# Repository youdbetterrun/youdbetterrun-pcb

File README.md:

# You'd Better Run!

Lets you know if you can walk leisurely to catch the bus, or if you'd better run.

This repository holds the printed circuit board design files. A render of the PCB is below.

There are separate repositories for the firmware and 3D models.
- [Firmware](https://github.com/youdbetterrun/youdbetterrun-firmware): The code that runs on the microcontroller.
- [3D](https://github.com/youdbetterrun/youdbetterrun-3d): 3D models that need to be 3D printed and assembly instructions.

[Blog post about this project.](https://blog.marcelrobitaille.me/youdbetterrun/)

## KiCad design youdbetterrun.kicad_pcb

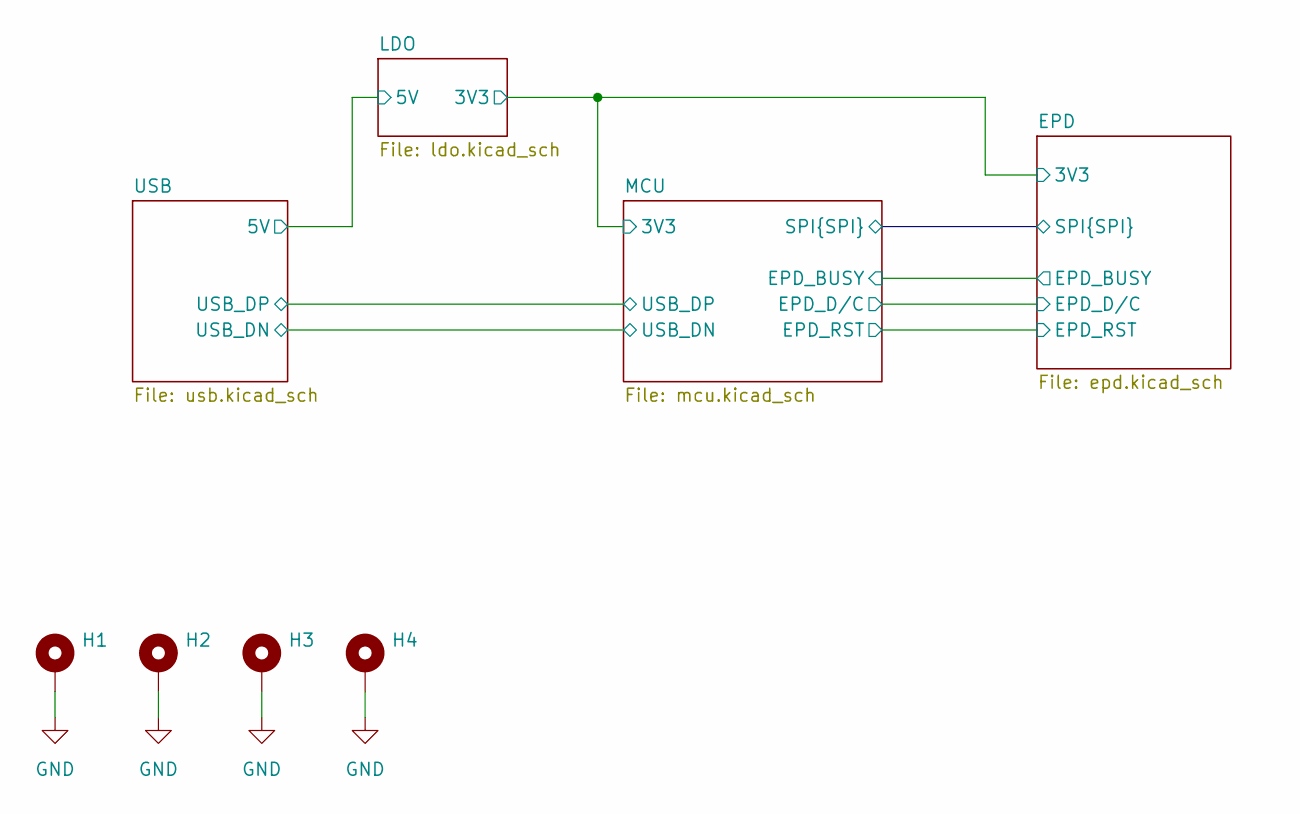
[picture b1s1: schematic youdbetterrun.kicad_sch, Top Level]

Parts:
H1, H2, H3, H4: MountingHole_Pad; MountingHole_2.2mm_M2_Pad

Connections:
GND: H1.1, H2.1, H3.1, H4.1; also elsewhere on the board

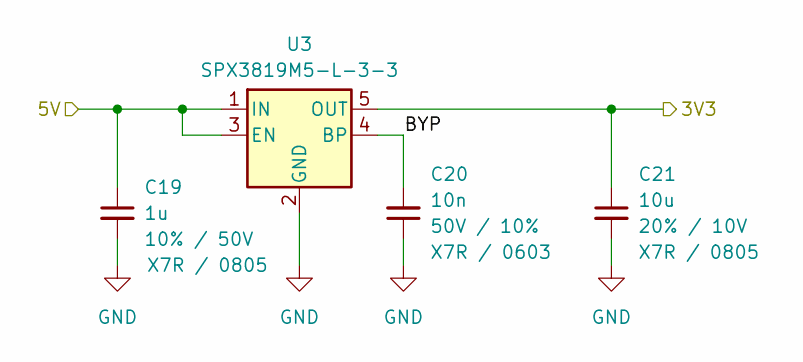
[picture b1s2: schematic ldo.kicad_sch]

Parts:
C19: 1u; C_0805_2012Metric; Tolerance 10%; Rated Voltage 50V; MPN CC0805KKX7R9BB105; LCSC Part Number C91185
C20: 10n; C_0603_1608Metric; Rated Voltage 50V; Tolerance 10%; MPN CC0603KRX7R9BB103; LCSC Part Number C100042
C21: 10u; C_0805_2012Metric; Rated Voltage 10V; Tolerance 20%; MPN CS2012X7R106M100NRE; LCSC Part Number C5189822
U3: SPX3819M5-L-3-3; SOT-23-5; MPN SPX3819M5-L-3-3/TR; LCSC Part Number C9055

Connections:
/EPD/3V3: C21.1, U3.5 (OUT); also elsewhere on the board
/LDO/BYP: C20.2, U3.4 (BP)
/USB/5V: C19.1, U3.1 (IN), U3.3 (EN); also elsewhere on the board
GND: C19.2, C20.1, C21.2, U3.2 (GND); also elsewhere on the board

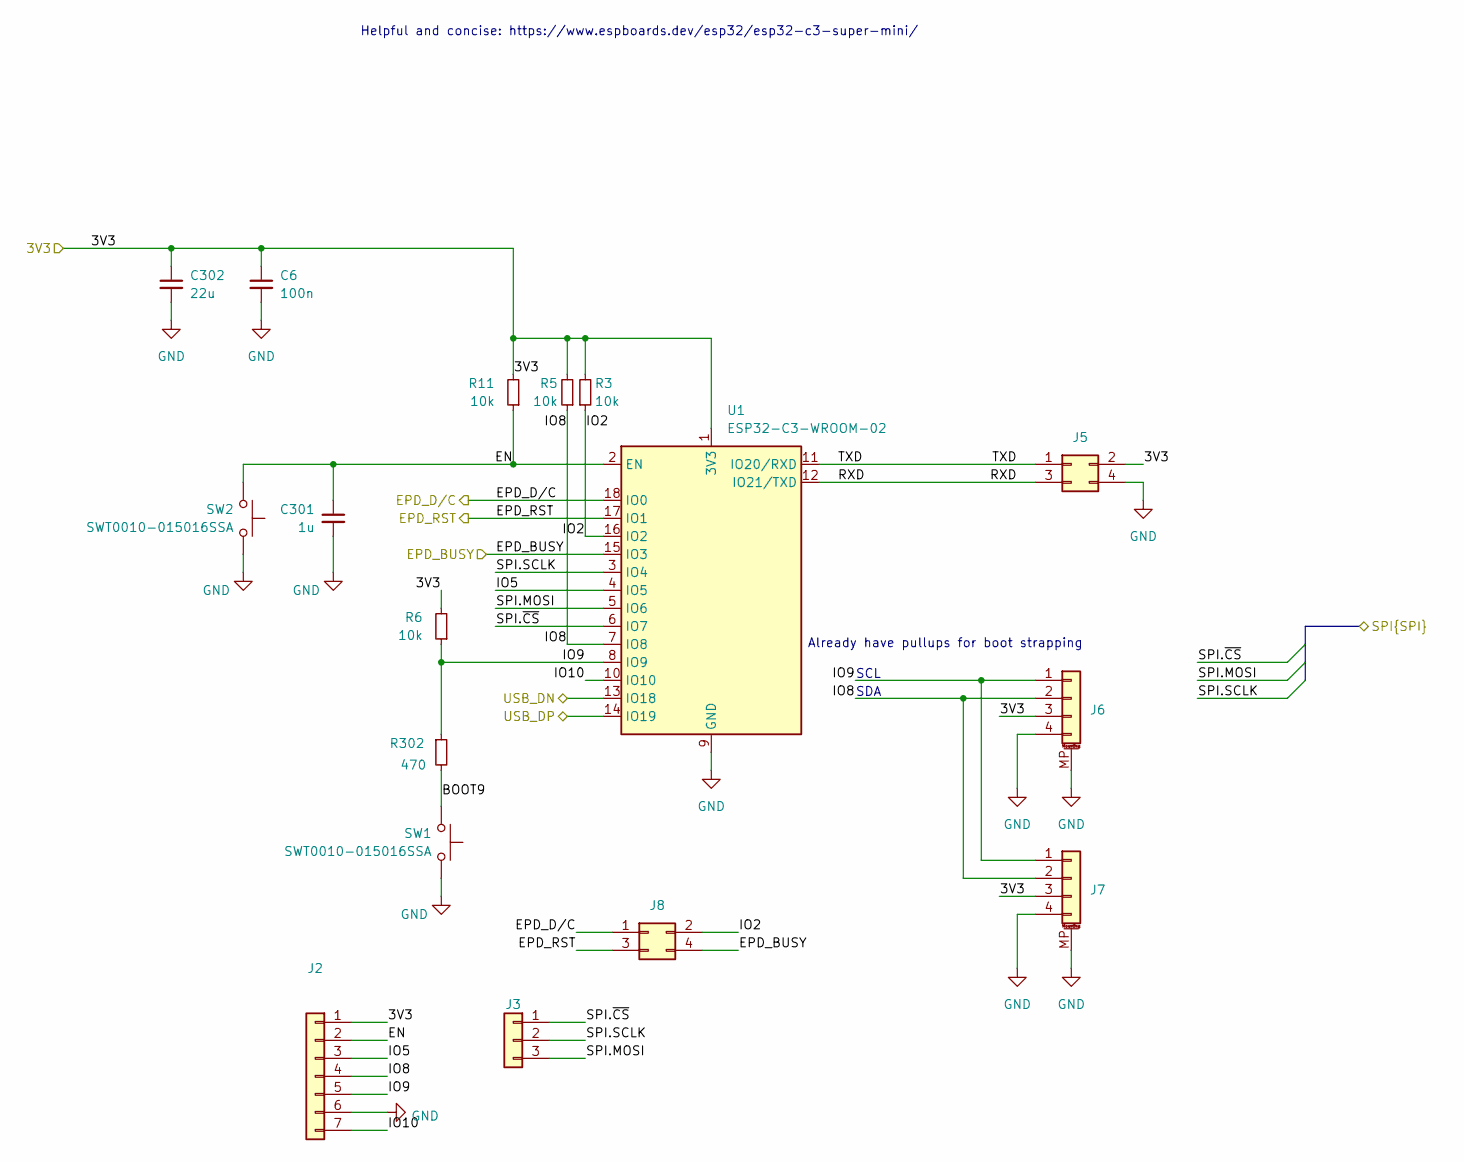
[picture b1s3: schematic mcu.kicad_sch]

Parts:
C6: 100n; C_0805_2012Metric; Rated Voltage 50V; Tolerance 10%; MPN 0805B104K500NT; LCSC Part Number C38141
C301: 1u; C_0805_2012Metric; Tolerance 10%; Rated Voltage 50V; MPN CC0805KKX7R9BB105; LCSC Part Number C91185
C302: 22u; C_0805_2012Metric
J2: Conn_01x05_Pin; PinHeader_1x07_P2.54mm_Vertical
J3: Conn_01x10_Pin; PinHeader_1x03_P2.54mm_Vertical
J5, J8: Conn_01x04; PinHeader_2x02_P2.54mm_Vertical
J6, J7: SM04B-SRSS-TB; JST_SH_SM04B-SRSS-TB_1x04-1MP_P1.00mm_Horizontal; MPN SM04B-SRSS-TB; Digikey Part Number 455-SM04B-SRSS-TBCT-ND
R3, R5, R6, R11: 10k; R_0805_2012Metric; Tolerance 1%; MPN 0805W8F1002T5E; LCSC Part Number C17414
R302: 470; R_0805_2012Metric
SW1, SW2: SWT0010-015016SSA; MPN SWT0010-015016SSA; Mouser Part Number 640-SWT0010015016SSA
U1: ESP32-C3-WROOM-02; ESP32-C3-WROOM-02_big_vias

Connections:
/EPD/3V3: C6.1, C302.1, J2.1, J5.2, J6.3, J7.3, R3.2, R5.2, R6.2, R11.2, U1.1 (3V3); also elsewhere on the board
/EPD/EPD_BUSY: J8.4, U1.15 (IO3); also elsewhere on the board
/EPD/EPD_D/C: J8.1, U1.18 (IO0); also elsewhere on the board
/EPD/EPD_RST: J8.3, U1.17 (IO1); also elsewhere on the board
/EPD/SPI.MOSI: J3.3, U1.5 (IO6); also elsewhere on the board
/EPD/SPI.SCLK: J3.2, U1.3 (IO4); also elsewhere on the board
/EPD/SPI.~CS: J3.1, U1.6 (IO7); also elsewhere on the board
/MCU/BOOT9: R302.2, SW1.2
/MCU/EN: C301.1, J2.2, R11.1, SW2.2, U1.2 (EN)
/MCU/IO2: J8.2, R3.1, U1.16 (IO2)
/MCU/IO5: J2.3, U1.4 (IO5)
/MCU/IO8: J2.4, J6.2, J7.2, R5.1, U1.7 (IO8)
/MCU/IO9: J2.5, J6.1, J7.1, R6.1, R302.1, U1.8 (IO9)
/MCU/IO10: J2.7, U1.10 (IO10)
/MCU/RXD: J5.3, U1.12 (IO21/TXD)
/MCU/TXD: J5.1, U1.11 (IO20/RXD)
/USB/USB_DN: U1.13 (IO18); also elsewhere on the board
/USB/USB_DP: U1.14 (IO19); also elsewhere on the board
GND: C6.2, C301.2, C302.2, J2.6, J5.4, J6.4, J6.MP (MountPin), J7.4, J7.MP (MountPin), SW1.1, SW2.1, U1.9 (GND), U1.19 (GND); also elsewhere on the board

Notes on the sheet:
SCL
Already have pullups for boot strapping
SDA
Helpful and concise: https://www.espboards.dev/esp32/esp32-c3-super-mini/

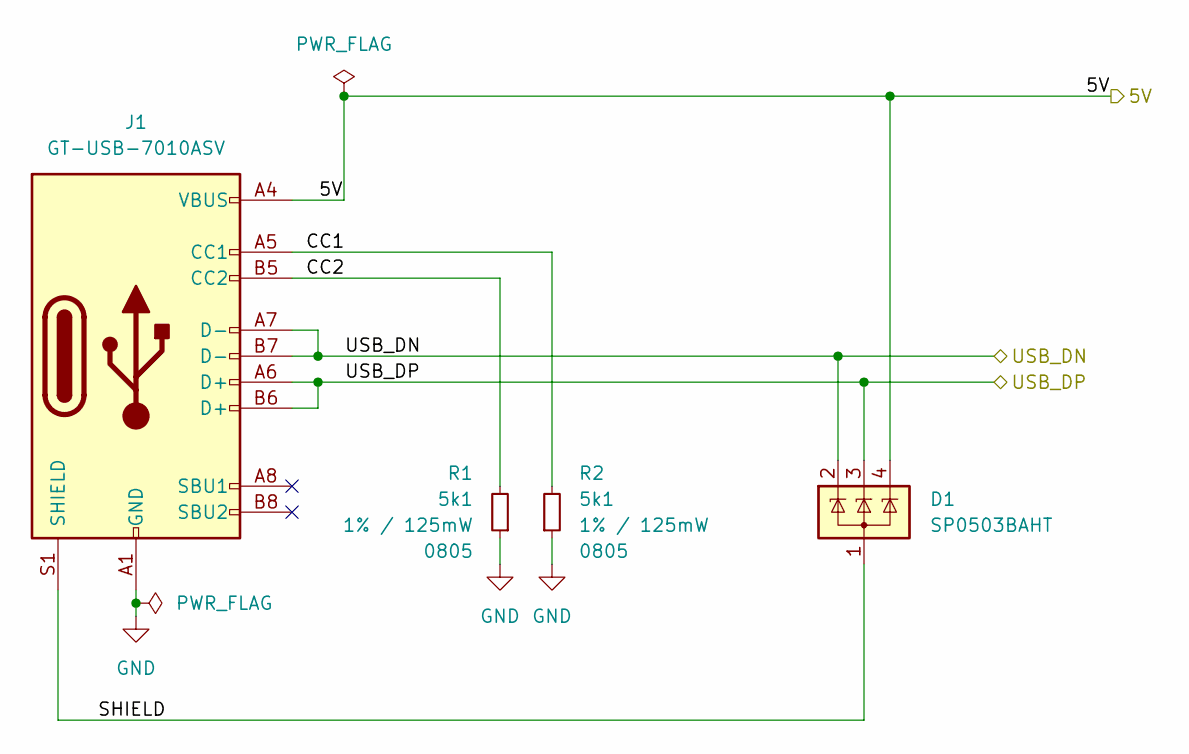
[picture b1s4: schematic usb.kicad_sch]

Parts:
D1: SP0503BAHT; SOT-143; MPN SP0503BAHTG; LCSC Part Number C7074
J1: GT-USB-7010ASV; USB_C_Receptacle_G-Switch_GT-USB-7010ASV; MPN G-Switch; LCSC Part Number C2988369
R1, R2: 5k1; R_0805_2012Metric; Tolerance 1%; MPN 0805W8F5101T5E; LCSC Part Number C27834

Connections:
/USB/5V: D1.4 (K), J1.A4 (VBUS), J1.A9 (VBUS), J1.B4 (VBUS), J1.B9 (VBUS); also elsewhere on the board
/USB/CC1: J1.A5 (CC1), R2.2
/USB/CC2: J1.B5 (CC2), R1.2
/USB/SHIELD: D1.1 (A), J1.S1 (SHIELD)
/USB/USB_DN: D1.2 (K), J1.A7 (D-), J1.B7 (D-); also elsewhere on the board
/USB/USB_DP: D1.3 (K), J1.A6 (D+), J1.B6 (D+); also elsewhere on the board
GND: J1.A1 (GND), J1.A12 (GND), J1.B1 (GND), J1.B12 (GND), R1.1, R2.1; also elsewhere on the board

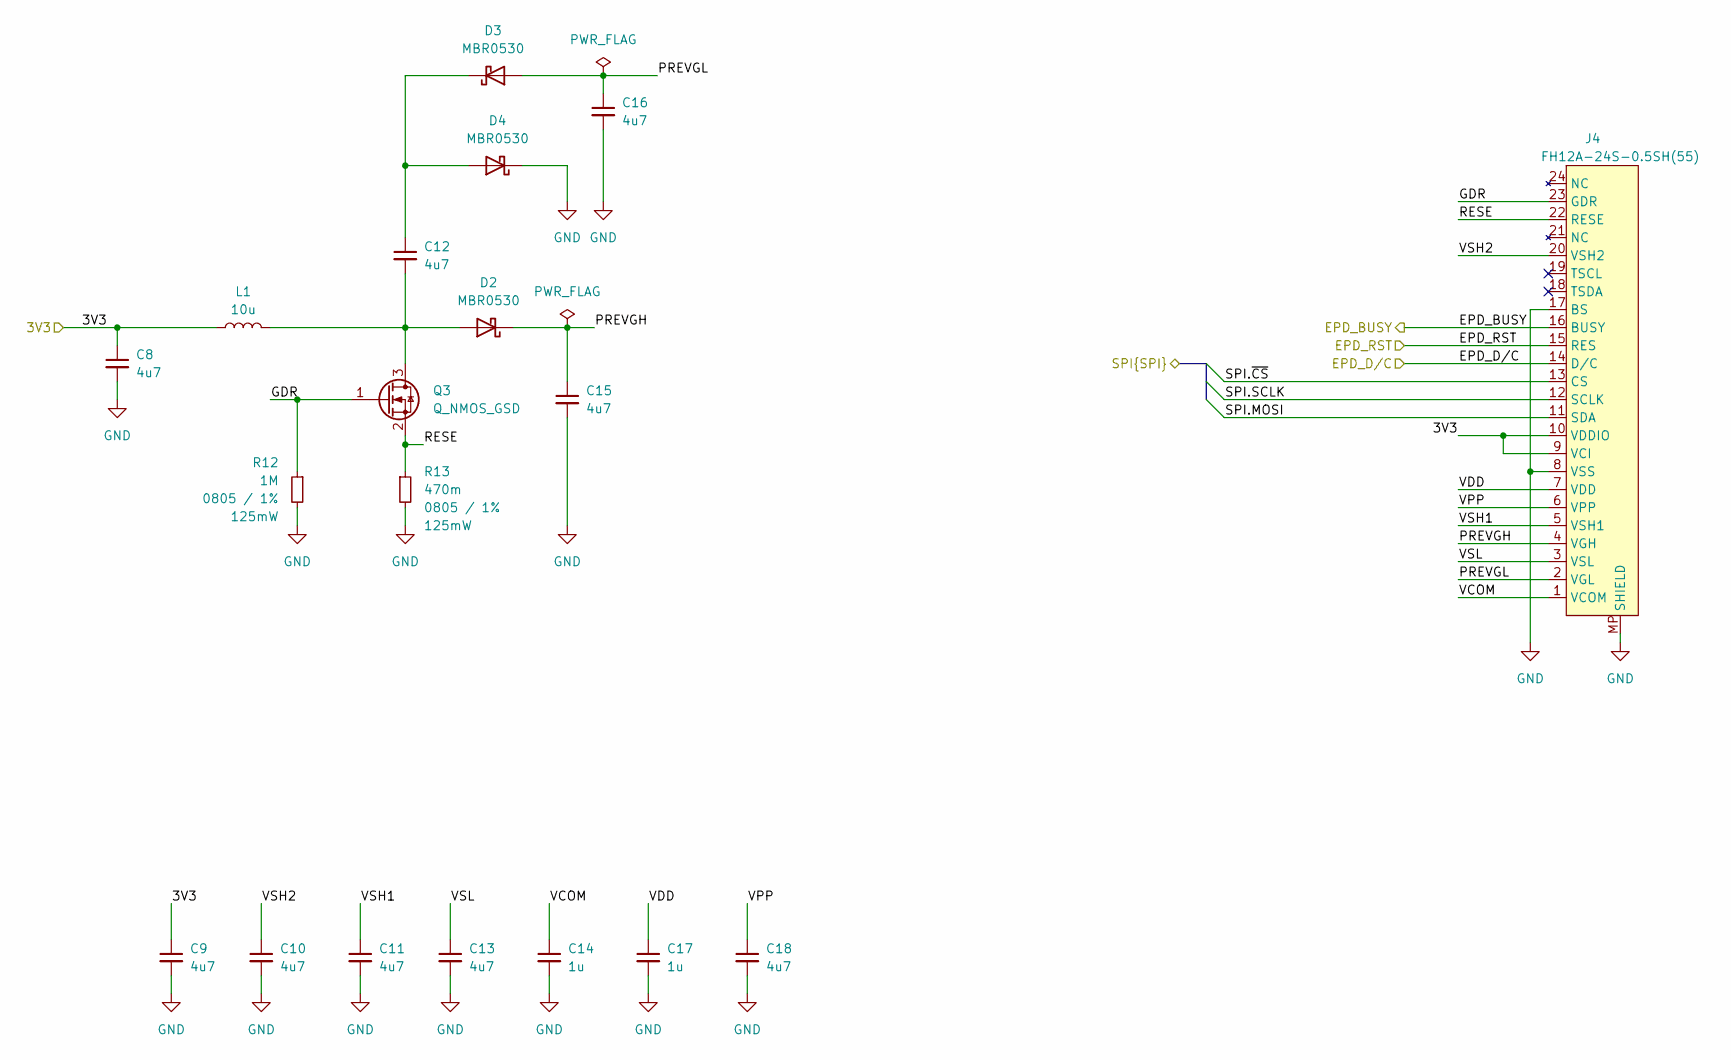
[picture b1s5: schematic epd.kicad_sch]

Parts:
C8, C9, C10, C11, C12, C13, C15, C16, C18: 4u7; C_0805_2012Metric; Tolerance 10%; Rated Voltage 50V; MPN CL21A475KBQNNNE; LCSC Part Number C98192
C14, C17: 1u; C_0805_2012Metric; Tolerance 10%; Rated Voltage 50V; MPN CC0805KKX7R9BB105; LCSC Part Number C91185
D2, D3, D4: MBR0530; D_SOD-123; MPN MBR0530; LCSC Part Number C77336
J4: FH12A-24S-0.5SH(55); Hirose_FH12-24S-0.5SH_1x24-1MP_P0.50mm_Horizontal; MPN FH12A-24S-0.5SH(55); LCSC Part Number C506794
L1: 10u; L_4x4x2.6; MPN YJYCOIN YNR4026-100M; LCSC Part Number C497803
Q3: Q_NMOS_GSD; SOT-323_SC-70; MPN SI1308EDL-T1-GE3; LCSC Part Number C469327
R12: 1M; R_0805_2012Metric; Tolerance 1%; MPN 0805W8F1004T5E; LCSC Part Number C17514
R13: 470m; R_0805_2012Metric; Tolerance 1%; MPN 0805W8F470LT5E; LCSC Part Number C25040

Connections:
/EPD/3V3: C8.1, C9.1, J4.9 (VCI), J4.10 (VDDIO), L1.1; also elsewhere on the board
/EPD/EPD_BUSY: J4.16 (BUSY); also elsewhere on the board
/EPD/EPD_D/C: J4.14 (D/C); also elsewhere on the board
/EPD/EPD_RST: J4.15 (RES); also elsewhere on the board
/EPD/GDR: J4.23 (GDR), Q3.1 (G), R12.1
/EPD/PREVGH: C15.1, D2.1 (K), J4.4 (VGH)
/EPD/PREVGL: C16.1, D3.2 (A), J4.2 (VGL)
/EPD/RESE: J4.22 (RESE), Q3.2 (S), R13.1
/EPD/SPI.MOSI: J4.11 (SDA); also elsewhere on the board
/EPD/SPI.SCLK: J4.12 (SCLK); also elsewhere on the board
/EPD/SPI.~CS: J4.13 (CS); also elsewhere on the board
/EPD/VCOM: C14.1, J4.1 (VCOM)
/EPD/VDD: C17.1, J4.7 (VDD)
/EPD/VPP: C18.1, J4.6 (VPP)
/EPD/VSH1: C11.1, J4.5 (VSH1)
/EPD/VSH2: C10.1, J4.20 (VSH2)
/EPD/VSL: C13.1, J4.3 (VSL)
GND: C8.2, C9.2, C10.2, C11.2, C13.2, C14.2, C15.2, C16.2, C17.2, C18.2, D4.1 (K), J4.8 (VSS), J4.17 (BS), J4.MP (SHIELD), R12.2, R13.2; also elsewhere on the board
unnamed: C12.2, D2.2 (A), L1.2, Q3.3 (D)
unnamed: C12.1, D3.1 (K), D4.2 (A)

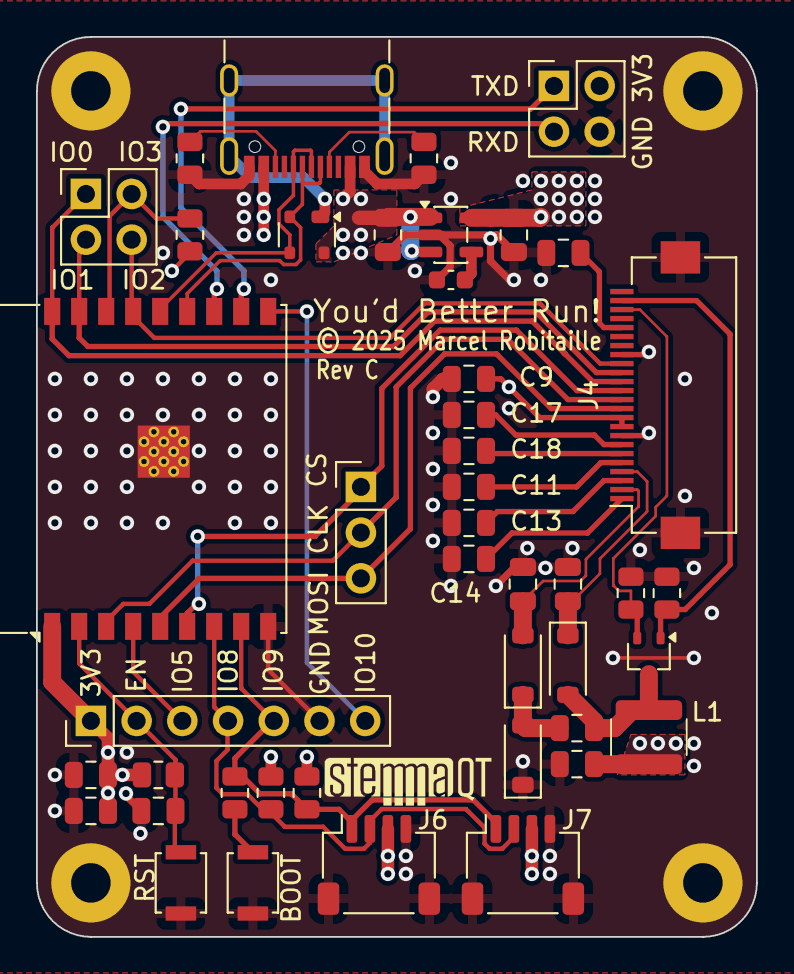
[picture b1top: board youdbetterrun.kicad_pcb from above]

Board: 4 copper layers, 40.0 x 50.0 mm, 49 parts (0 on the bottom side), 36 nets.

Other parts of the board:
StemmaQTLogo: STEMMAQT

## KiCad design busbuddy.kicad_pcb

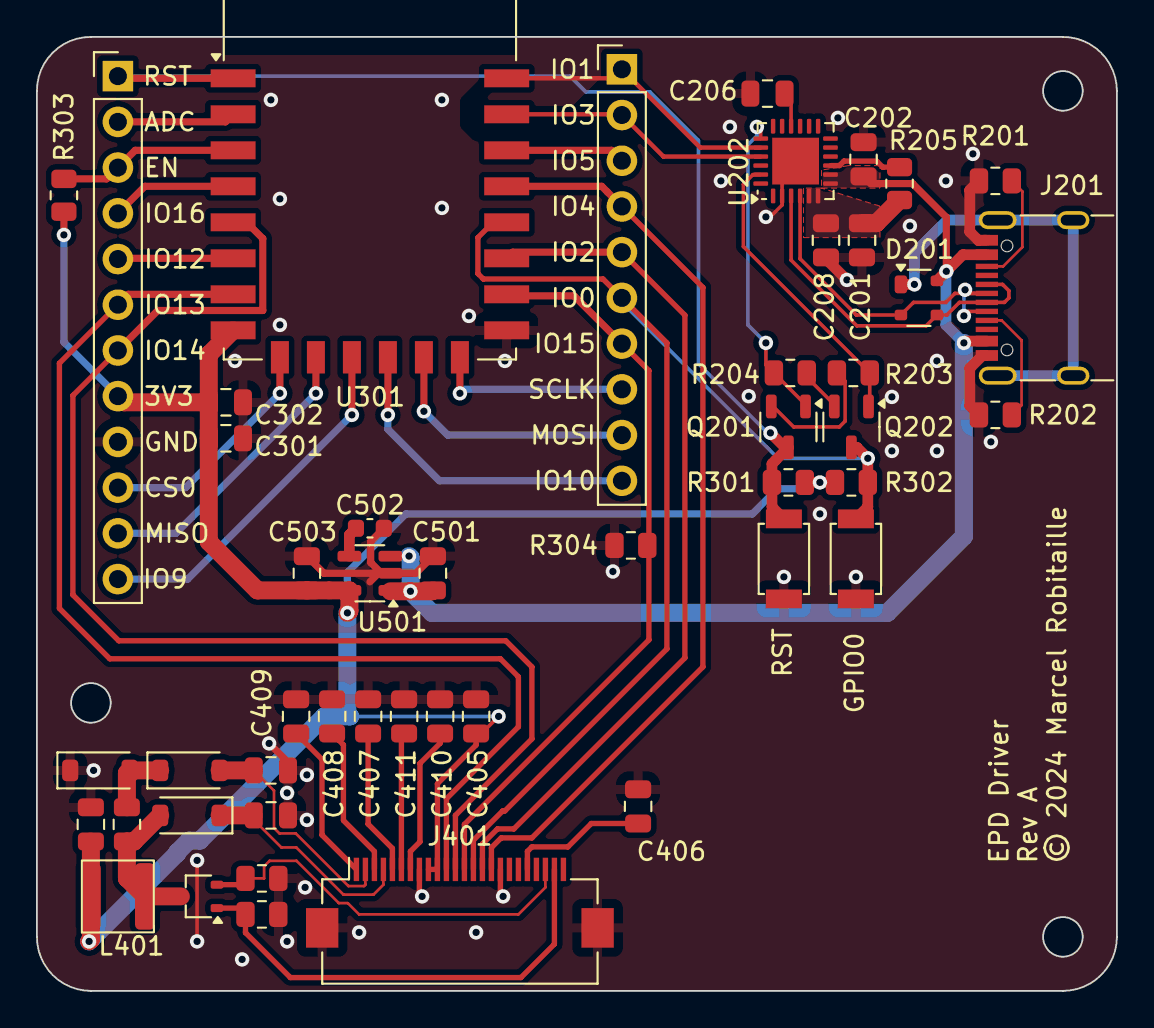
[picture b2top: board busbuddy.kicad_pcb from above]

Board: 4 copper layers, 60.0 x 53.0 mm, 48 parts (0 on the bottom side), 48 nets.

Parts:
C201, C206, C401, C402, C403, C404, C405, C406, C407, C408, C411: 4u7; C_0805_2012Metric
C202, C208, C302: 100n; C_0805_2012Metric
C301, C503: 10u; C_0805_2012Metric
C409, C410, C501: 1u; C_0805_2012Metric
C502: 10n; C_0603_1608Metric
D201: SP0503BAHT; SOT-143
D401, D402, D403: MBR0530; D_SOD-123
J201: GT-USB-7010ASV; USB_C_Receptacle_G-Switch_GT-USB-7010ASV
J301: Conn_01x05_Pin; PinHeader_1x12_P2.54mm_Vertical
J302: Conn_01x10_Pin; PinHeader_1x10_P2.54mm_Vertical
J401: FH12A-24S-0.5SH(55); Hirose_FH12-24S-0.5SH_1x24-1MP_P0.50mm_Horizontal
L401: 10u; L_4x4x2.6
Q201, Q202: S8050; SOT-23-3
Q401: Q_NMOS_GSD; SOT-323_SC-70
R201, R202: 5k1; R_0805_2012Metric
R203, R204: 12k; R_0805_2012Metric
R205: 4k7; R_0805_2012Metric
R301, R302, R303, R304: 10k; R_0805_2012Metric
R401: 470m; R_0805_2012Metric
R402: 1M; R_0805_2012Metric
SW301, SW302: TS-1088R-02026; TS-1088R-02026_SW_SMD_3x4mm
U202: CP2104; QFN-24-1EP_4x4mm_P0.5mm_EP2.6x2.6mm
U301: ESP-12F; ESP-12E
U501: SPX3819M5-L-3-3; SOT-23-5

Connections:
/EPD/3V3: C301.1, C302.1, C402.1, C405.1, C503.1, J301.8, J401.9 (VCI), J401.10 (VDDIO), L401.1, R301.2, R302.1, R303.2, U301.8 (VCC), U501.5 (OUT)
/EPD/EPD_BUSY: J302.4, J401.16 (BUSY), U301.19 (GPIO4)
/EPD/EPD_D/C: J302.6, J401.14 (D/C), Q202.3 (C), R302.2, SW302.2, U301.18 (GPIO0)
/EPD/EPD_RST: J302.5, J401.15 (RES), U301.17 (GPIO2)
/EPD/GDR: J401.23 (GDR), Q401.1 (G), R402.1
/EPD/PREVGH: C401.1, D401.1 (K), J401.4 (VGH)
/EPD/PREVGL: C404.1, D403.2 (A), J401.2 (VGL)
/EPD/RESE: J401.22 (RESE), Q401.2 (S), R401.1
/EPD/SPI.MOSI: J301.6, J401.11 (SDA), U301.7 (GPIO13)
/EPD/SPI.SCLK: J301.7, J401.12 (SCLK), U301.5 (GPIO14)
/EPD/SPI.~CS: J302.7, J401.13 (CS), R304.1, U301.16 (GPIO15)
/EPD/VCOM: C409.1, J401.1 (VCOM)
/EPD/VDD: C410.1, J401.7 (VDD)
/EPD/VPP: C411.1, J401.6 (VPP)
/EPD/VSH1: C407.1, J401.5 (VSH1)
/EPD/VSH2: C406.1, J401.20 (VSH2)
/EPD/VSL: C408.1, J401.3 (VSL)
/LDO/BYP: C502.2, U501.4 (BP)
/MCU/ADC: J301.2, U301.2 (ADC)
/MCU/CS0: J301.10, U301.9 (CS0)
/MCU/EN: J301.3, R303.1, U301.3 (EN)
/MCU/GPIO5: J302.3, U301.20 (GPIO5)
/MCU/GPIO9: J301.12, U301.11 (GPIO9)
/MCU/GPIO10: J302.10, U301.12 (GPIO10)
/MCU/GPIO12: J301.5, U301.6 (GPIO12)
/MCU/GPIO16: J301.4, U301.4 (GPIO16)
/MCU/MISO: J301.11, U301.10 (MISO)
/MCU/MOSI: J302.9, U301.13 (MOSI)
/MCU/RXD: J302.2, U202.21 (TXD), U301.21 (GPIO3/RXD)
/MCU/SCLK: J302.8, U301.14 (SCLK)
/MCU/TXD: J302.1, U202.20 (RXD), U301.22 (GPIO1/TXD)
/MCU/~RST: J301.1, Q201.3 (C), R301.1, SW301.2, U301.1 (~RST)
/USB/5V: C202.1, C501.1, D201.4 (K), J201.A4 (VBUS), J201.A9 (VBUS), J201.B4 (VBUS), J201.B9 (VBUS), U202.7 (REGIN), U202.8 (VBUS), U501.1 (IN), U501.3 (EN)
/USB/CC1: J201.A5 (CC1), R202.2
/USB/CC2: J201.B5 (CC2), R201.2
/USB/CP2104_~RST: R205.2, U202.9 (~RST)
/USB/D+: D201.3 (K), J201.A6 (D+), J201.B6 (D+), U202.3 (D+)
/USB/D-: D201.2 (K), J201.A7 (D-), J201.B7 (D-), U202.4 (D-)
/USB/SHIELD: D201.1 (A), J201.S1 (SHIELD)
/USB/VIO: C201.1, C208.1, R205.1, U202.5 (VIO), U202.6 (VDD)
/USB/VPP: C206.1, U202.16 (VPP)
/USB/~DTR: Q202.1 (E), R203.1, U202.23 (~DTR)
/USB/~RTS: Q201.1 (E), R204.1, U202.19 (~RTS)
GND: C201.2, C202.2, C206.2, C208.2, C301.2, C302.2, C401.2, C402.2, C404.2, C405.2, C406.2, C407.2, C408.2, C409.2, C410.2, C411.2, C501.2, C502.1, C503.2, D402.1 (K), J201.A1 (GND), J201.A12 (GND), J201.B1 (GND), J201.B12 (GND), J301.9, J401.8 (VSS), J401.17 (BS), J401.MP (SHIELD), R201.1, R202.1, R304.2, R401.2, R402.2, SW301.1, SW302.1, U202.2 (GND), U202.25 (GND), U301.15 (GND), U501.2 (GND)
unnamed: C403.2, D401.2 (A), L401.2, Q401.3 (D)
unnamed: C403.1, D402.2 (A), D403.1 (K)
unnamed: Q201.2 (B), R203.2
unnamed: Q202.2 (B), R204.2

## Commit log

2024-03-10 Remove CH340G
2024-05-11 Switch to 16 pin USB-C
2024-05-11 Correct SPI pinout
2024-05-26 Finish everything
2024-12-17 DRC exclusions
2024-12-17 Rename project
    Damn squatters
2024-12-17 Ignore kiri folder
2024-12-17 Add OSHW logo
2024-12-17 Add README.md
2025-01-17 Link to blog post
2025-10-26 Switch to ESP32
2025-11-10 Fixes

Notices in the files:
busbuddy.kicad_pcb:
© 2024 Marcel Robitaille
youdbetterrun.kicad_pcb:
© 2025 Marcel Robitaille
